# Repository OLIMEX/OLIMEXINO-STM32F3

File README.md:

# OLIMEXINO-STM32F3
Industrial grade -40+85C Arduino IDE programmable board with STM32F303RCT6TR Cortex-M4 CAN and USB

# OLIMEXINO-GD32F3
Industrial grade -40+85C Arduino IDE programmable board with GD32F303RCT6 Cortex-M4 CAN and USB

Product page: https://www.olimex.com/Products/Duino/STM32/OLIMEXINO-STM32F3/open-source-hardware

## Licensee
* Hardware is released under CERN Open Hardware Licence Version 2 -
Strongly Reciprocal
* Software is released under GPL3 Licensee
* Documentation is released under CC BY-SA 3.0

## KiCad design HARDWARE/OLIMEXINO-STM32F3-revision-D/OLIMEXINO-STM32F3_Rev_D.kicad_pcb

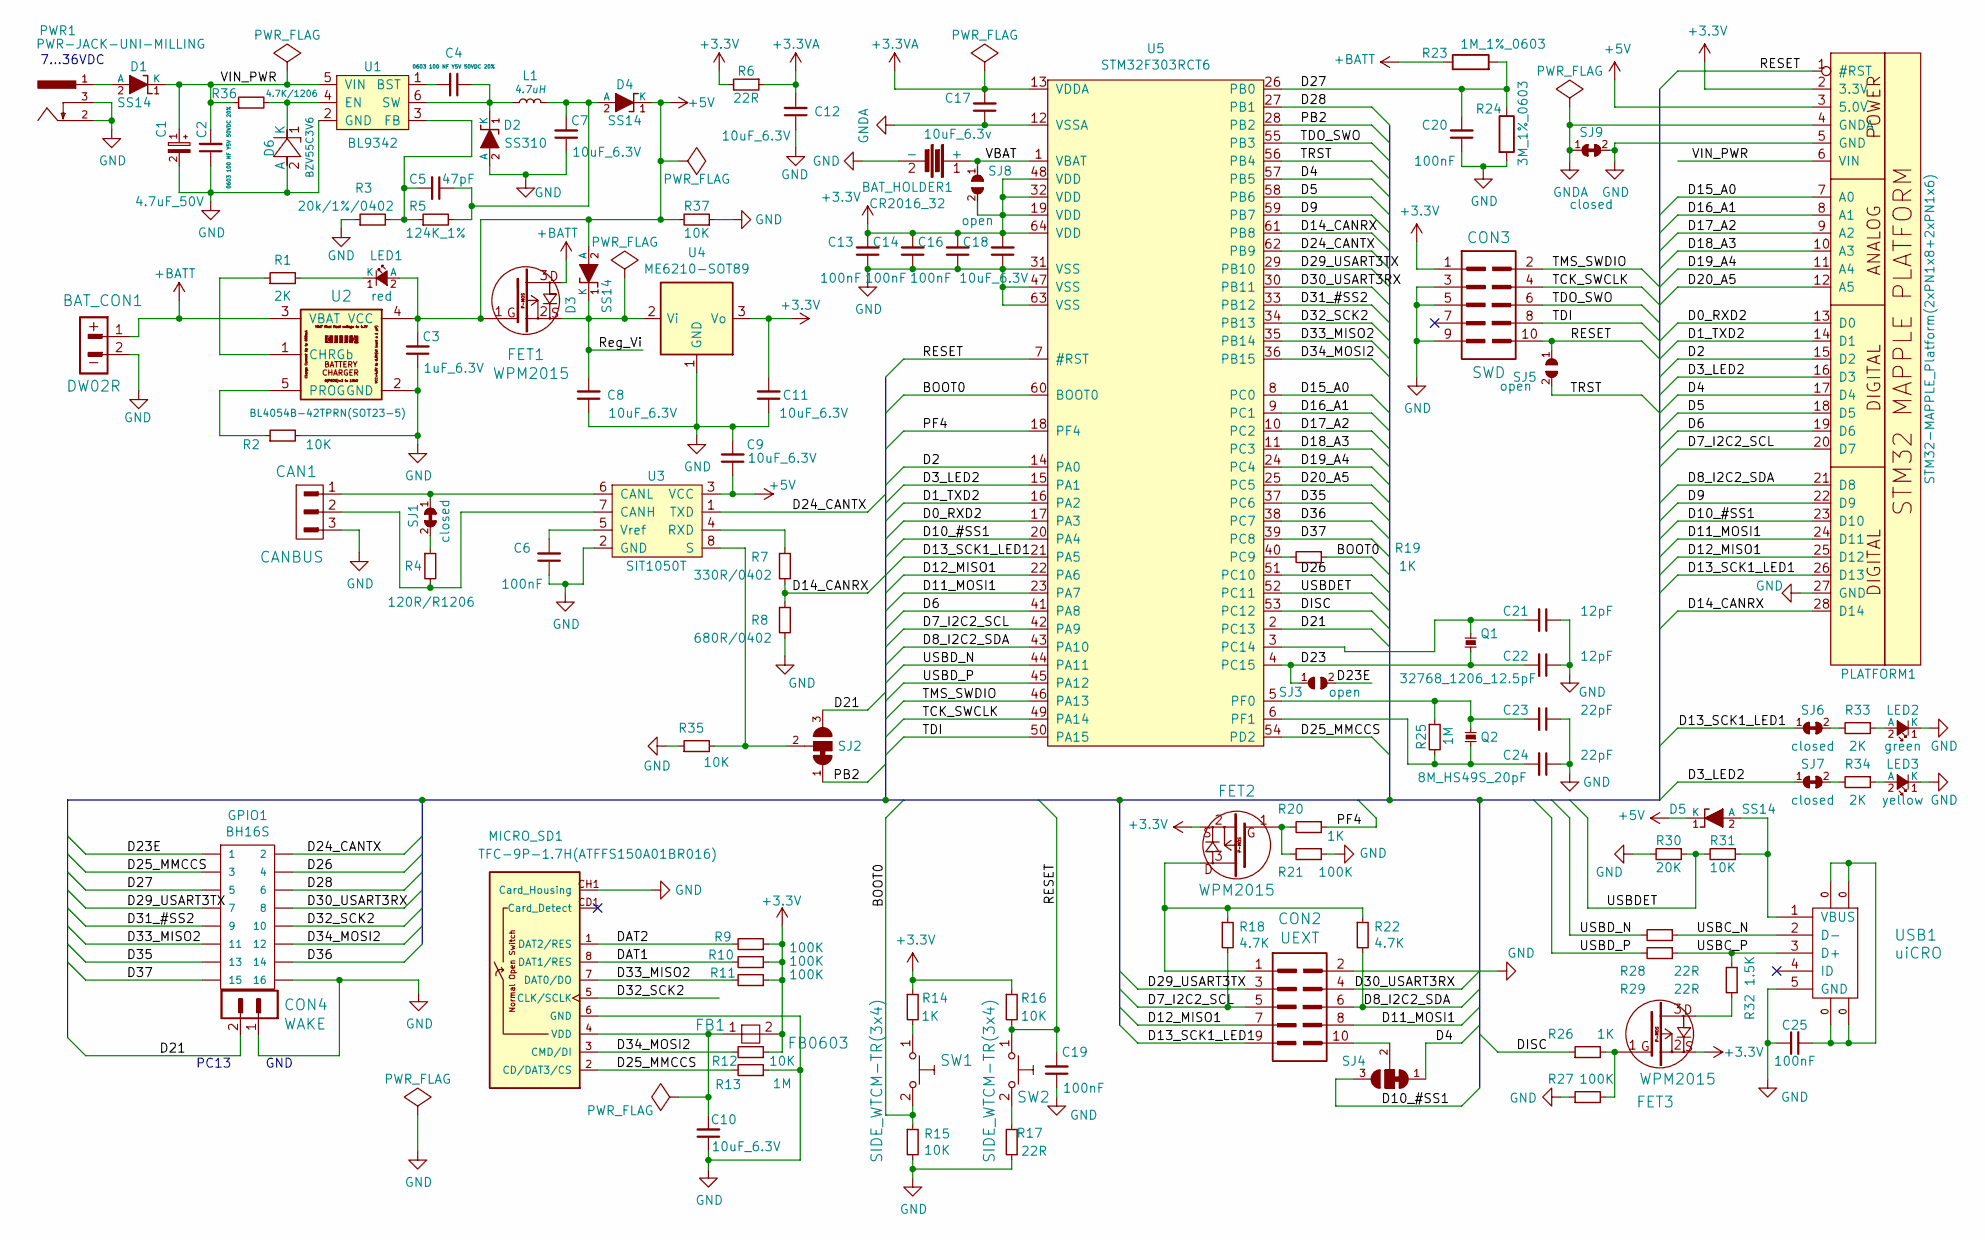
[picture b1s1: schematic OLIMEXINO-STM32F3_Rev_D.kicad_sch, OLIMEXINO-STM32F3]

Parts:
BAT_CON1: DW02R; LIPO_BAT-CON2DW02R
BAT_HOLDER1: CR2016_32; CR2032-PTH-PLASTIC
C1: 4.7uF_50V; CPOL-RM2mm_5x9mm_PTH
C2, C4: 0603 100 NF Y5V 50VDC 20%; C_0603_5MIL_DWS
C3: 1uF_6.3V; C_0603_5MIL_DWS
C5: 47pF; C_0402_5MIL_DWS
C6, C13, C14, C16, C19, C20, C25: 100nF; C_0402_5MIL_DWS
C7, C8, C9, C10, C11, C12, C18: 10uF_6.3V; C_0603_5MIL_DWS
C17: 10uF_6.3v; C_0603_5MIL_DWS
C21, C22: 12pF; C_0402_5MIL_DWS
C23, C24: 22pF; C_0402_5MIL_DWS
CAN1: CANBUS; TB3-3.5mm
CON2: UEXT; UEXT_BH10R
CON3: SWD; GPH127SMT-02X05(PA-V16X-2X5-LF)
CON4: WAKE; HN1x2
D1, D3, D4, D5: SS14; SMA-KA
D2: SS310; SMA-KA
D6: BZV55C3V6; SOD80C-4148-KA
FB1: FB0603; L_0603_5MIL_DWS
FET1, FET2, FET3: WPM2015; SOT23
GPIO1: BH16S
L1: 4.7uH; CD43
LED1: red; LED_0603_KA
LED2: green; LED_0603_KA
LED3: yellow; LED_0603_KA
MICRO_SD1: TFC-9P-1.7H(ATFFS150A01BR016); uSD(TFC-9P-1.xH(ATFFS150A01BR016))
PLATFORM1: STM32-MAPPLE_Platform(2xPN1x8+2xPN1x6); ARDUINO-STM32-PLATFORM
PWR1: PWR-JACK-UNI-MILLING; PWR_JACK_UNI_MILLING
Q1: 32768_1206_12.5pF; L_1206_5MIL_DWS
Q2: 8M_HS49S_20pF; Q_49U3HMS
R1, R33, R34: 2K; R_0402_5MIL_DWS
R2, R12, R15, R16, R31, R35, R37: 10K; R_0402_5MIL_DWS
R3: 20k/1%/0402; R_0402_5MIL_DWS
R4: 120R/R1206; R_1206_5MIL_DWS
R5: 124K_1%; R_0402_5MIL_DWS
R6, R17, R28, R29: 22R; R_0402_5MIL_DWS
R7: 330R/0402; R_0402_5MIL_DWS
R8: 680R/0402; R_0402_5MIL_DWS
R9, R10, R11, R21, R27: 100K; R_0402_5MIL_DWS
R13, R25: 1M; R_0402_5MIL_DWS
R14, R19, R20, R26: 1K; R_0402_5MIL_DWS
R18, R22: 4.7K; R_0402_5MIL_DWS
R23: 1M_1%_0603; R_0603_5MIL_DWS
R24: 3M_1%_0603; R_0603_5MIL_DWS
R30: 20K; R_0402_5MIL_DWS
R32: 1.5K; R_0402_5MIL_DWS
R36: 4.7K/1206; R_1206_5MIL_DWS
SJ1, SJ6, SJ7, SJ9: closed; SJ_Closed
SJ2, SJ4: SJ2W_Closed(1-2); SJ_2_SMALL_12_TIED
SJ3, SJ5, SJ8: open; SJ
SW1, SW2: SIDE_WTCM-TR(3x4); TSW34-W16PR-220
U1: BL9342; SOT23-6
U2: BL4054B-42TPRN(SOT23-5); SOT-23-5
U3: SIT1050T; SO-8
U4: ME6210-SOT89; SOT89
U5: STM32F303RCT6; LQFP64_Pitch-0.5mm_12.00x12.00x1.60mm
USB1: uiCRO; USB-MICRO_MISB-SWMM-5B_LF

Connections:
+3.3V: C11.2, C13.2, C14.2, C16.2, C18.2, CON3.1, FB1.2, FET2.2, FET3.2, PLATFORM1.2 (3.3V), R6.2, R9.1, R10.1, R11.1, R12.1, R14.1, R16.1, SJ8.2, U4.3 (Vo), U5.19 (VDD), U5.32 (VDD), U5.48 (VDD), U5.64 (VDD)
+3.3VA: C12.2, C17.2, R6.1, U5.13 (VDDA)
+5V: C3.2, C9.1, D3.2 (A), D4.1 (K), D5.1 (K), FET1.1, LED1.2 (A), PLATFORM1.3 (5.0V), R37.2, U2.4 (VCC), U3.3 (VCC)
+BATT: BAT_CON1.1, FET1.3, R23.1, U2.3 (VBAT)
/BOOT0: R15.1, R19.1, SW1.2, U5.60 (BOOT0)
/D0_RXD2: PLATFORM1.13 (D0), U5.17 (PA3)
/D1_TXD2: PLATFORM1.14 (D1), U5.16 (PA2)
/D2: PLATFORM1.15 (D2), U5.14 (PA0)
/D3_LED2: PLATFORM1.16 (D3), SJ7.1, U5.15 (PA1)
/D4: PLATFORM1.17 (D4), SJ4.1, U5.57 (PB5)
/D5: PLATFORM1.18 (D5), U5.58 (PB6)
/D6: PLATFORM1.19 (D6), U5.41 (PA8)
/D7_I2C2_SCL: CON2.5, PLATFORM1.20 (D7), R18.2, U5.42 (PA9)
/D8_I2C2_SDA: CON2.6, PLATFORM1.21 (D8), R22.2, U5.43 (PA10)
/D9: PLATFORM1.22 (D9), U5.59 (PB7)
/D10_#SS1: PLATFORM1.23 (D10), SJ4.3, U5.20 (PA4)
/D11_MOSI1: CON2.8, PLATFORM1.24 (D11), U5.23 (PA7)
/D12_MISO1: CON2.7, PLATFORM1.25 (D12), U5.22 (PA6)
/D13_SCK1_LED1: CON2.9, PLATFORM1.26 (D13), SJ6.1, U5.21 (PA5)
/D14_CANRX: PLATFORM1.28 (D14), R7.2, R8.1, U5.61 (PB8)
/D15_A0: PLATFORM1.7 (A0), U5.8 (PC0)
/D16_A1: PLATFORM1.8 (A1), U5.9 (PC1)
/D17_A2: PLATFORM1.9 (A2), U5.10 (PC2)
/D18_A3: PLATFORM1.10 (A3), U5.11 (PC3)
/D19_A4: PLATFORM1.11 (A4), U5.24 (PC4)
/D20_A5: PLATFORM1.12 (A5), U5.25 (PC5)
/D21: CON4.2, SJ2.3, U5.2 (PC13)
/D23: C22.2, Q1.1, SJ3.1, U5.4 (PC15)
/D23E: GPIO1.1, SJ3.2
/D24_CANTX: GPIO1.2, U3.1 (TXD), U5.62 (PB9)
/D25_MMCCS: GPIO1.3, MICRO_SD1.2 (CD/DAT3/CS), R13.2, U5.54 (PD2)
/D26: GPIO1.4, U5.51 (PC10)
/D27: C20.2, GPIO1.5, R23.2, R24.1, U5.26 (PB0)
/D28: GPIO1.6, U5.27 (PB1)
/D29_USART3TX: CON2.3, GPIO1.7, U5.29 (PB10)
/D30_USART3RX: CON2.4, GPIO1.8, U5.30 (PB11)
/D31_#SS2: GPIO1.9, U5.33 (PB12)
/D32_SCK2: GPIO1.10, MICRO_SD1.5 (CLK/SCLK), U5.34 (PB13)
/D33_MISO2: GPIO1.11, MICRO_SD1.7 (DAT0/DO), R11.2, U5.35 (PB14)
/D34_MOSI2: GPIO1.12, MICRO_SD1.3 (CMD/DI), R12.2, U5.36 (PB15)
/D35: GPIO1.13, U5.37 (PC6)
/D36: GPIO1.14, U5.38 (PC7)
/D37: GPIO1.15, U5.39 (PC8)
/DAT1: MICRO_SD1.8 (DAT1/RES), R10.2
/DAT2: MICRO_SD1.1 (DAT2/RES), R9.2
/DISC: R26.1, U5.53 (PC12)
/PB2: SJ2.1, U5.28 (PB2)
/PF4: R20.1, U5.18 (PF4)
/RESET: C19.2, CON3.10, PLATFORM1.1 (#RST), R16.2, SJ5.1, SW2.1, U5.7 (#RST)
/Reg_Vi: C8.2, D3.1 (K), FET1.2, U4.2 (Vi)
/TCK_SWCLK: CON3.4, U5.49 (PA14)
/TDI: CON3.8, U5.50 (PA15)
/TDO_SWO: CON3.6, U5.55 (PB3)
/TMS_SWDIO: CON3.2, U5.46 (PA13)
/TRST: SJ5.2, U5.56 (PB4)
/USBC_N: R28.1, USB1.2 (D-)
/USBC_P: R29.1, R32.2, USB1.3 (D+)
/USBDET: R30.1, R31.2, U5.52 (PC11)
/USBD_N: R28.2, U5.44 (PA11)
/USBD_P: R29.2, U5.45 (PA12)
/VBAT: BAT_HOLDER1.1 (+), SJ8.1, U5.1 (VBAT)
/VIN_PWR: C1.1 (+), C2.2, D1.1 (K), PLATFORM1.6 (VIN), R36.1, U1.5 (VIN)
GND: BAT_CON1.2, BAT_HOLDER1.2 (-), C1.2 (-), C2.1, C3.1, C6.1, C7.1, C8.1, C9.2, C10.1, C11.1, C12.1, C13.1, C14.1, C16.1, C18.1, C19.1, C20.1, C21.1, C22.1, C23.1, C24.1, C25.1, CAN1.3, CON2.2, CON3.3, CON3.5, CON3.9, CON4.1, D2.2 (A), D6.2 (A), GPIO1.16, LED2.1 (K), LED3.1 (K), MICRO_SD1.6 (GND), MICRO_SD1.CH1 (Card_Housing), PLATFORM1.5 (GND), PLATFORM1.27 (GND), PWR1.2 (-), PWR1.3 (-), R2.2, R3.1, R8.2, R13.1, R15.2, R17.1, R21.1, R24.2, R27.1, R30.2, R35.1, R37.1, SJ9.2, U1.2 (GND), U2.2 (GND), U3.2 (GND), U4.1 (GND), U5.31 (VSS), U5.47 (VSS), U5.63 (VSS), USB1.5 (GND)
GNDA: C17.1, PLATFORM1.4 (GNDA), SJ9.1, U5.12 (VSSA)
unnamed: C25.2, USB1.0
unnamed: CON2.1, FET2.3, R18.1, R22.1
unnamed: CON2.10, SJ4.2
unnamed: D1.2 (A), PWR1.1 (+)
unnamed: C4.1, D2.1 (K), L1.1, U1.6 (SW)
unnamed: C5.1, C7.2, D4.2 (A), L1.2, R5.2
unnamed: D5.2 (A), R31.1, USB1.1 (VBUS)
unnamed: D6.1 (K), R36.2, U1.4 (EN)
unnamed: FET2.1, R20.2, R21.2
unnamed: FET3.1, R26.2, R27.2
unnamed: FET3.3, R32.1
unnamed: LED1.1 (K), R1.2
unnamed: LED2.2 (A), R33.1
unnamed: LED3.2 (A), R34.1
unnamed: C10.2, FB1.1, MICRO_SD1.4 (VDD)
unnamed: R4.1, SJ1.2
unnamed: R14.2, SW1.1
unnamed: R17.2, SW2.2
unnamed: R33.2, SJ6.2
unnamed: R34.2, SJ7.2
unnamed: C4.2, U1.1 (BST)
unnamed: C5.2, R3.2, R5.1, U1.3 (FB)
unnamed: R1.1, U2.1 (CHRGb)
unnamed: R2.1, U2.5 (PROG)
unnamed: CAN1.2, R4.2, U3.7 (CANH)
unnamed: CAN1.1, SJ1.1, U3.6 (CANL)
unnamed: R7.1, U3.4 (RXD)
unnamed: R35.2, SJ2.2, U3.8 (S)
unnamed: C6.2, U3.5 (Vref)
unnamed: R19.2, U5.40 (PC9)
unnamed: C21.2, Q1.2, U5.3 (PC14)
unnamed: C23.2, Q2.2, R25.1, U5.5 (PF0)
unnamed: C24.2, Q2.1, R25.2, U5.6 (PF1)

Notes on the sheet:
PC13 GND
7...36VDC

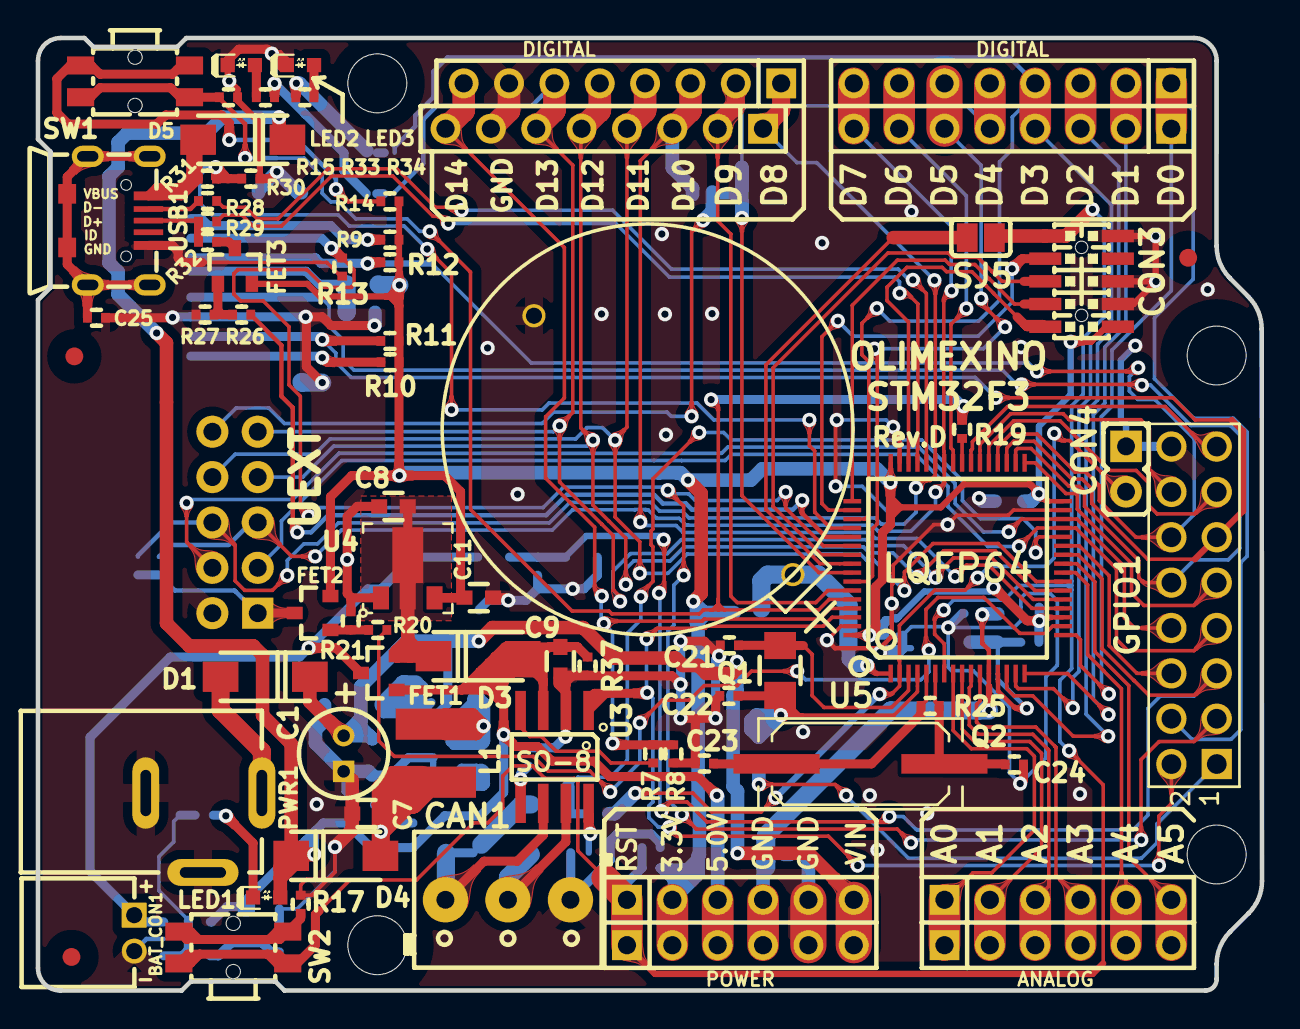
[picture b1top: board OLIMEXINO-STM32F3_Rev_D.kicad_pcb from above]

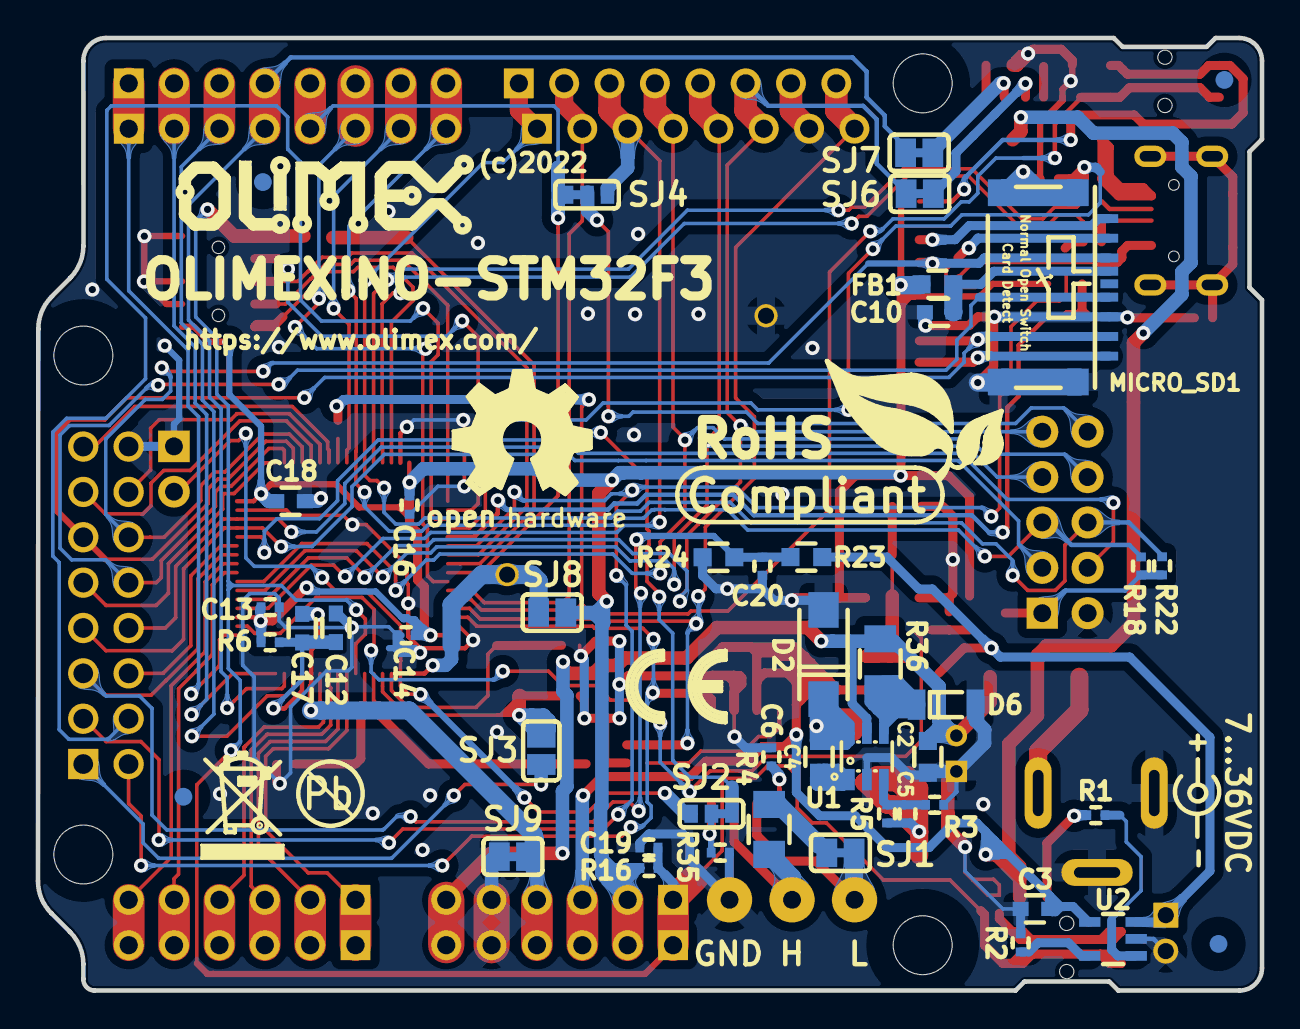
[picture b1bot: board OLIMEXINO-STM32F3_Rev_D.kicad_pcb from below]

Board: 2 copper layers, 68.5 x 53.3 mm, 117 parts (51 on the bottom side), 97 nets.

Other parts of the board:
FID1: FID1; Fiducial1x3_transp
FID2: FID2; Fiducial1x3_transp
FID3: FID3; Fiducial1x3_transp
FID4: FID4; Fiducial1x3_transp
FID5: FID5; Fiducial1x3_transp
FID6: FID6; Fiducial1x3_transp
FID7: FID7; Fiducial1x3_transp
Sign_CE: CE_Sign
Sign_OSHW: Sign_OSHW; LOGO_OPENHARDWARE_8x8
Sign_Olimex: Sign_Olimex; OLIMEX_LOGO_TB
Sign_PB-Free: PB-Free; LOGO_PBFREE
Sign_RecycleBin: Sign_RecycleBin; LOGO_RECYCLEBIN_1
Sign_RoHS_1: Sign_RoHS_1

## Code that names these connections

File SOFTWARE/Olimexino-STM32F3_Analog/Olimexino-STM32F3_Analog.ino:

#define SERIAL  Serial

int Time, PrevTime=0;

void setup()
{
  SERIAL.begin (115200);
  SERIAL.println ("Welcome!");
}

void loop()
{
  Time = millis ();
  if (Time >= PrevTime + 1000)
  {
    PrevTime = Time;
    SERIAL.print("\f");
    SERIAL.print("PC0 (D15/A0) = "); SERIAL.println (analogRead(A0));
    SERIAL.print("PC1 (D16/A1) = "); SERIAL.println (analogRead(A1));
    SERIAL.print("PC2 (D17/A2) = "); SERIAL.println (analogRead(A2));
    SERIAL.print("PC3 (D18/A3) = "); SERIAL.println (analogRead(A3));
    SERIAL.print("PC4 (D19/A4) = "); SERIAL.println (analogRead(A4));
    SERIAL.print("PC5 (D20/A5) = "); SERIAL.println (analogRead(A5));
  }
}

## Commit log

2020-07-31 initial upload
2020-10-02 Translate
    Translated some instructions to English
2020-11-21 HARDWARE/OLIMEXINO-STM32F3-RevB: drop unnecessary _autosave-OLIMEXINO-STM32F3_RevA.sch
2020-11-21 HARDWARE/OLIMEXINO-STM32F3-RevB: schematic: drop out-of-the-field unconnected D26 label
2020-11-21 HARDWARE/OLIMEXINO-STM32F3-RevB: add .gitignore
2022-09-22 Update
    Improved STM32F3 manual and added GD32F3 bootloader and blink demo
2022-12-02 Update
    GD32F3 specifics
2024-03-27 Examples update
    Examples updated to work with the latest version (at the moment of this commit 2.7.1) of the STM32-duino package.
    The examples affected are moved into the "Old" folder with the package patch files applied to 1.9.0 version of the STM32-duino.
2025-09-12 Update
    Updated OLIMEXINO-STM32 Arduino IDE instructions
2025-09-12 Update
    New hardware revision and updated manual

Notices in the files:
HARDWARE/OLIMEXINO-STM32F3-revision-D/OLIMEXINO-STM32F3_Rev_D.kicad_pcb:
(c)2022
